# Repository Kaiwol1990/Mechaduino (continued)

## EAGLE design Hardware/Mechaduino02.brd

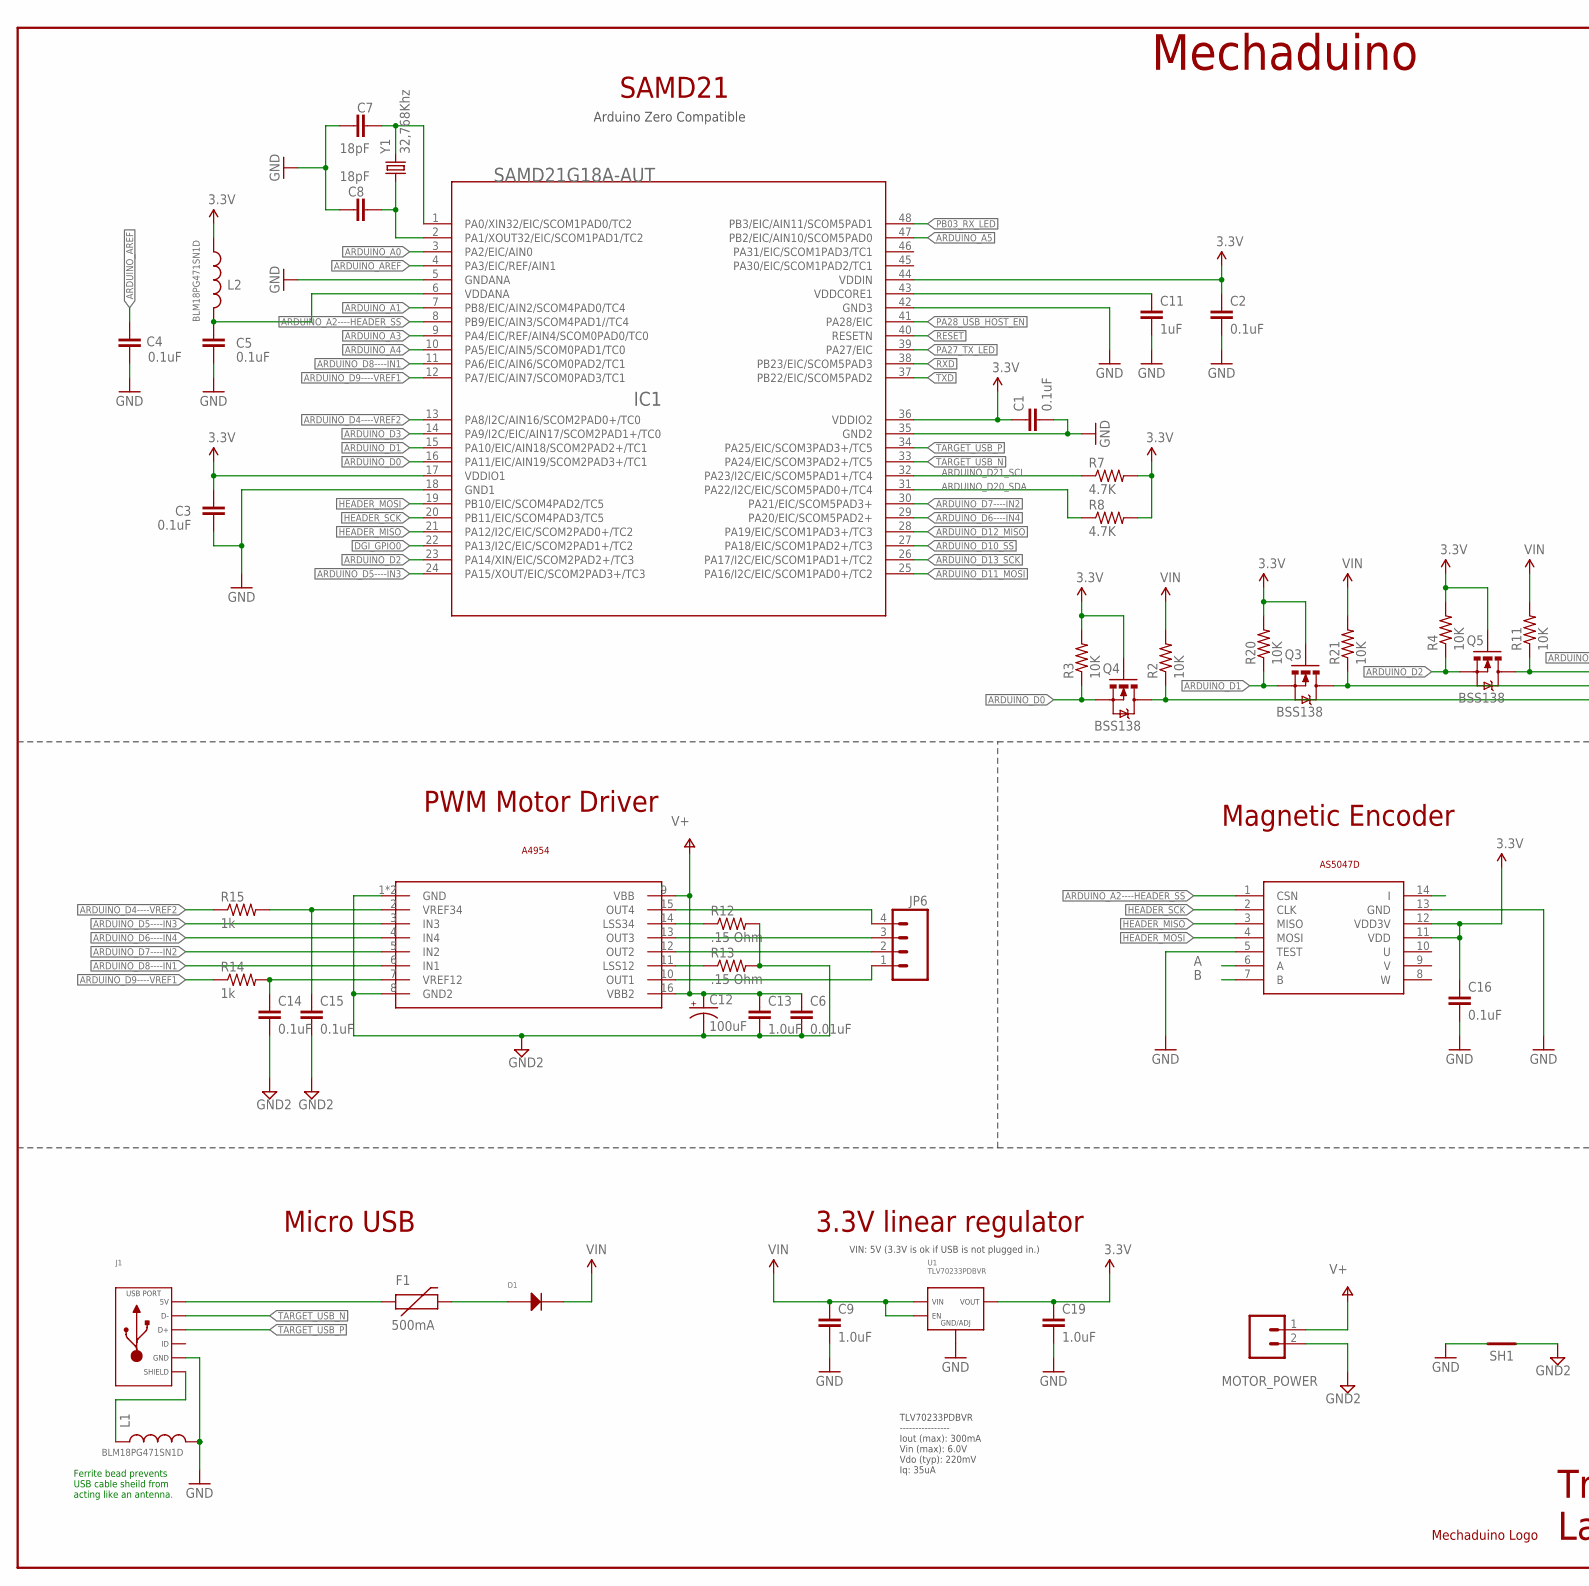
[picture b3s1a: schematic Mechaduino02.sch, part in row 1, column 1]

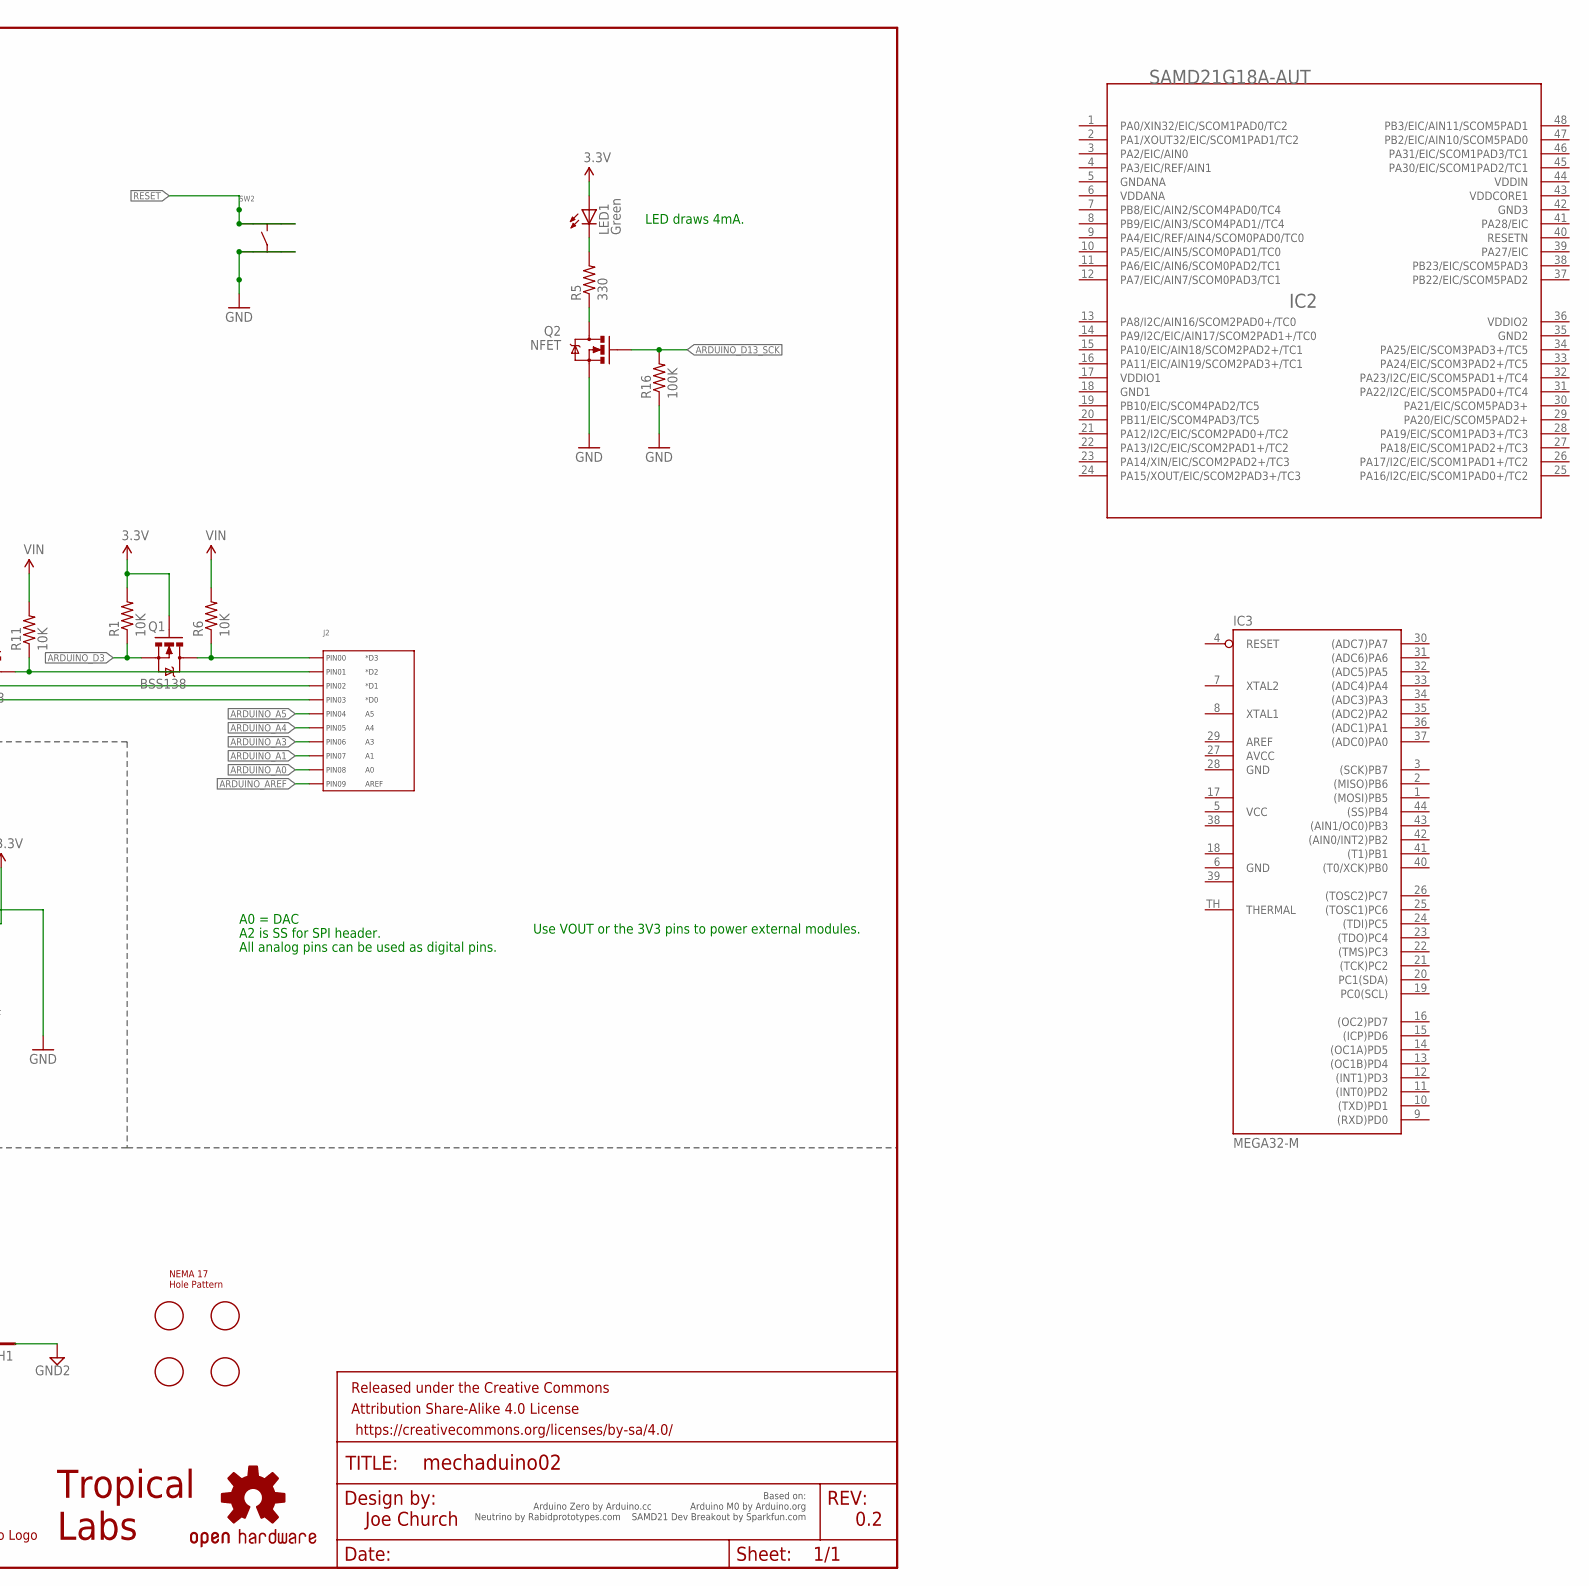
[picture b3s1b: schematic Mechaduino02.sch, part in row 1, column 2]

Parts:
C1, C2, C3, C4, C5, C14, C15, C16: 0.1uF; 0402-CAP
C6: 0.01uF; 0603-CAP
C7, C8: 18pF; 0603-CAP
C9, C19: 1.0uF; 0402-CAP
C11: 1uF; 0402-CAP
C12: 100uF; PANASONIC_D
C13: 1.0uF; 0603-CAP
D1: DIODE_SOD-123; SOD-123
F1: 500mA; PTC-1206
FRAME1: FRAME-LEDGER; CREATIVE_COMMONS
IC1, IC2: SAMD21G18A-AUT; INTEGRATEDCIRCUITS_TQFP48-7X7
IC3: MEGA32-M; MLF44-TH
J1: USB_MICRO_RIGHT; MICROUSB-RIGHT
J2: HEADER_01X10_PTH_2.54MM; PTH_2.54MM_01X10
JP6: M04PTH; 1X04
L1, L2: BLM18PG471SN1D; 0603-TDK
LED1: Green; CHIPLED_0805
LOGO4: OSHW-LOGOMOD; OSHW_LOGO_COPPER_MOD
MOTOR_POWER: M025MM; SCREWTERMINAL-5MM-2
Q1, Q3, Q4, Q5: BSS138; SOT23-3
Q2: NFET; SOT323
R1, R2, R3, R4, R6, R11, R20, R21: 10K; R0402-VISHAY
R5: 330; R0402-VISHAY
R7, R8: 4.7K; R0402-VISHAY
R12, R13: .15 Ohm; R1206
R14, R15: 1k; R0402-VISHAY
R16: 100K; R0402-VISHAY
SH1: SHORT-HA5; SHORT_ALL-50
SW2: TACT_4.2MM; TACT4.2MM
U1: TLV70233PDBVR; SOT-23-5
U$1: AVAGO_DRIVERTHERM; TSSOP16_THERM
U$2: NEMA17_HOLE_PATTERNNEW; NEMA17_HOLE_PATTERN_2
U$3: TROPICAL_LABS_LOGO_1LOGO3; LOGO3
U$4: AS5047D; TSSOP14
U$5: MECHADUINO_LOGO
Y1: 32,768Khz; CRYSTAL-SMD-2.0X1.2

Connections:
3.3V: C1.1, C2.1, C3.2, C16.1, C19.1, IC1.17 (VDDIO1), IC1.36 (VDDIO2), IC1.44 (VDDIN), L2.1, LED1.A, Q1.1 (G), Q3.1 (G), Q4.1 (G), Q5.1 (G), R1.2, R3.2, R4.2, R7.2, R8.2, R20.2, U1.P$5 (VOUT), U$4.11 (VDD), U$4.12 (VDD3V)
A: U$4.6 (A)
ARDUINO_A0: IC1.3 (PA2/EIC/AIN0), J2.P$9 (PIN8)
ARDUINO_A1: IC1.7 (PB8/EIC/AIN2/SCOM4PAD0/TC4), J2.P$8 (PIN7)
ARDUINO_A2----HEADER_SS: IC1.8 (PB9/EIC/AIN3/SCOM4PAD1//TC4), U$4.1 (CSN)
ARDUINO_A3: IC1.9 (PA4/EIC/REF/AIN4/SCOM0PAD0/TC0), J2.P$7 (PIN6)
ARDUINO_A4: IC1.10 (PA5/EIC/AIN5/SCOM0PAD1/TC0), J2.P$6 (PIN5)
ARDUINO_A5: IC1.47 (PB2/EIC/AIN10/SCOM5PAD0), J2.P$5 (PIN4)
ARDUINO_AREF: C4.1, IC1.4 (PA3/EIC/REF/AIN1), J2.P$10 (PIN9)
ARDUINO_D0: IC1.16 (PA11/EIC/AIN19/SCOM2PAD3+/TC1), Q4.2 (S), R3.1
ARDUINO_D1: IC1.15 (PA10/EIC/AIN18/SCOM2PAD2+/TC1), Q3.2 (S), R20.1
ARDUINO_D2: IC1.23 (PA14/XIN/EIC/SCOM2PAD2+/TC3), Q5.2 (S), R4.1
ARDUINO_D3: IC1.14 (PA9/I2C/EIC/AIN17/SCOM2PAD1+/TC0), Q1.2 (S), R1.1
ARDUINO_D4----VREF2: IC1.13 (PA8/I2C/AIN16/SCOM2PAD0+/TC0), R15.1
ARDUINO_D5----IN3: IC1.24 (PA15/XOUT/EIC/SCOM2PAD3+/TC3), U$1.3 (IN3)
ARDUINO_D6----IN4: IC1.29 (PA20/EIC/SCOM5PAD2+), U$1.4 (IN4)
ARDUINO_D7----IN2: IC1.30 (PA21/EIC/SCOM5PAD3+), U$1.5 (IN2)
ARDUINO_D8----IN1: IC1.11 (PA6/EIC/AIN6/SCOM0PAD2/TC1), U$1.6 (IN1)
ARDUINO_D9----VREF1: IC1.12 (PA7/EIC/AIN7/SCOM0PAD3/TC1), R14.1
ARDUINO_D10_SS: IC1.27 (PA18/EIC/SCOM1PAD2+/TC3)
ARDUINO_D11_MOSI: IC1.25 (PA16/I2C/EIC/SCOM1PAD0+/TC2)
ARDUINO_D12_MISO: IC1.28 (PA19/EIC/SCOM1PAD3+/TC3)
ARDUINO_D13_SCK: IC1.26 (PA17/I2C/EIC/SCOM1PAD1+/TC2), Q2.1 (G), R16.2
ARDUINO_D20_SDA: IC1.31 (PA22/I2C/EIC/SCOM5PAD0+/TC4), R8.1
ARDUINO_D21_SCL: IC1.32 (PA23/I2C/EIC/SCOM5PAD1+/TC4), R7.1
AVCC: IC3.27 (AVCC)
B: U$4.7 (B)
DGI_GPIO0: IC1.22 (PA13/I2C/EIC/SCOM2PAD1+/TC2)
GND: C1.2, C2.2, C3.1, C4.2, C5.2, C7.1, C8.1, C9.2, C11.2, C16.2, C19.2, IC1.5 (GNDANA), IC1.18 (GND1), IC1.35 (GND2), IC1.42 (GND3), IC3.6 (GND), IC3.28 (GND), J1.5 (GND), L1.2, Q2.2 (S), R16.1, SH1.2, SW2.P$3, SW2.P$4, U1.P$2 (GND/ADJ), U$4.5 (TEST), U$4.13 (GND)
GND1: IC2.18 (GND1), IC3.18 (GND1)
GND2: C6.2, C12.-, C13.2, C14.2, C15.2, IC2.35 (GND2), IC3.39 (GND2), MOTOR_POWER.2, R12.2, R13.2, SH1.1, U$1.1 (GND), U$1.8 (GND2), U$1.P$1 (GND)
GND3: IC2.42 (GND3)
GNDANA: IC2.5 (GNDANA)
HEADER_MISO: IC1.21 (PA12/I2C/EIC/SCOM2PAD0+/TC2), U$4.3 (MISO)
HEADER_MOSI: IC1.19 (PB10/EIC/SCOM4PAD2/TC5), U$4.4 (MOSI)
HEADER_SCK: IC1.20 (PB11/EIC/SCOM4PAD3/TC5), U$4.2 (CLK)
HV1: J2.P$3 (PIN2), Q3.3 (D), R21.1
HV2: J2.P$4 (PIN3), Q4.3 (D), R2.1
HV3: J2.P$2 (PIN1), Q5.3 (D), R11.1
HV4: J2.P$1 (PIN0), Q1.3 (D), R6.1
I: U$4.14 (I)
unnamed: LED1.C, R5.2
unnamed: R12.1, U$1.14 (LSS34)
unnamed: Q2.3 (D), R5.1
unnamed: R13.1, U$1.11 (LSS12)
unnamed: C15.1, R15.2, U$1.2 (VREF34)
unnamed: JP6.4, U$1.15 (OUT4)
unnamed: JP6.1, U$1.10 (OUT1)
unnamed: JP6.2, U$1.12 (OUT2)
unnamed: JP6.3, U$1.13 (OUT3)
unnamed: C14.1, R14.2, U$1.7 (VREF12)
unnamed: D1.ANODE, F1.2
unnamed: F1.1, J1.1 (5V)
PA00_XIN32: C7.2, IC1.1 (PA0/XIN32/EIC/SCOM1PAD0/TC2), Y1.2
PA01_XOUT32: C8.2, IC1.2 (PA1/XOUT32/EIC/SCOM1PAD1/TC2), Y1.1
PA27_TX_LED: IC1.39 (PA27/EIC)
PA28_USB_HOST_EN: IC1.41 (PA28/EIC)
PB03_RX_LED: IC1.48 (PB3/EIC/AIN11/SCOM5PAD1)
RESET: IC1.40 (RESETN), SW2.P$1, SW2.P$2
RXD: IC1.38 (PB23/EIC/SCOM5PAD3)
SHIELD: J1.S1 (SLD), J1.S2 (SLD), J1.S3 (SLD), J1.S4 (SLD), J1.S5 (SLD), J1.S6 (SLD), J1.S7 (SLD), J1.S8 (SLD), L1.1
TARGET_USB_N: IC1.33 (PA24/EIC/SCOM3PAD2+/TC5), J1.2 (D-)
TARGET_USB_P: IC1.34 (PA25/EIC/SCOM3PAD3+/TC5), J1.3 (D+)
TXD: IC1.37 (PB22/EIC/SCOM5PAD2)
V+: C6.1, C12.+, C13.1, MOTOR_POWER.1, U$1.9 (VBB), U$1.16 (VBB2)
VCC: IC3.5 (VCC)
VCC1: IC3.17 (VCC1)
VCC2: IC3.38 (VCC2)
VDDANA: C5.1, IC1.6 (VDDANA), IC2.6 (VDDANA), L2.2
VDDCORE: C11.1, IC1.43 (VDDCORE1)
VDDIN: IC2.44 (VDDIN)
VDDIO1: IC2.17 (VDDIO1)
VDDIO2: IC2.36 (VDDIO2)
VIN: C9.1, D1.CATHODE, R2.2, R6.2, R11.2, R21.2, U1.P$1 (VIN), U1.P$3 (EN)

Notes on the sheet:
A0 = DAC
All analog pins can be used as digital pins.
LED draws 4mA.
A2 is SS for SPI header.
Use VOUT or the 3V3 pins to power external modules.
Ferrite bead prevents USB cable sheild from acting like an antenna.
3.3V linear regulator
Magnetic Encoder
SAMD21
PWM Motor Driver
VIN: 5V (3.3V is ok if USB is not plugged in.)
TLV70233PDBVR ---------------- Iout (max): 300mA Vin (max): 6.0V Vdo (typ): 220mV Iq: 35uA
A4954
Micro USB
Joe Church
Based on: Arduino Zero by Arduino.cc Arduino M0 by Arduino.org Neutrino by Rabidprototypes.com SAMD21 Dev Breakout by Sparkfun.com
0.2
Arduino Zero Compatible
Mechaduino

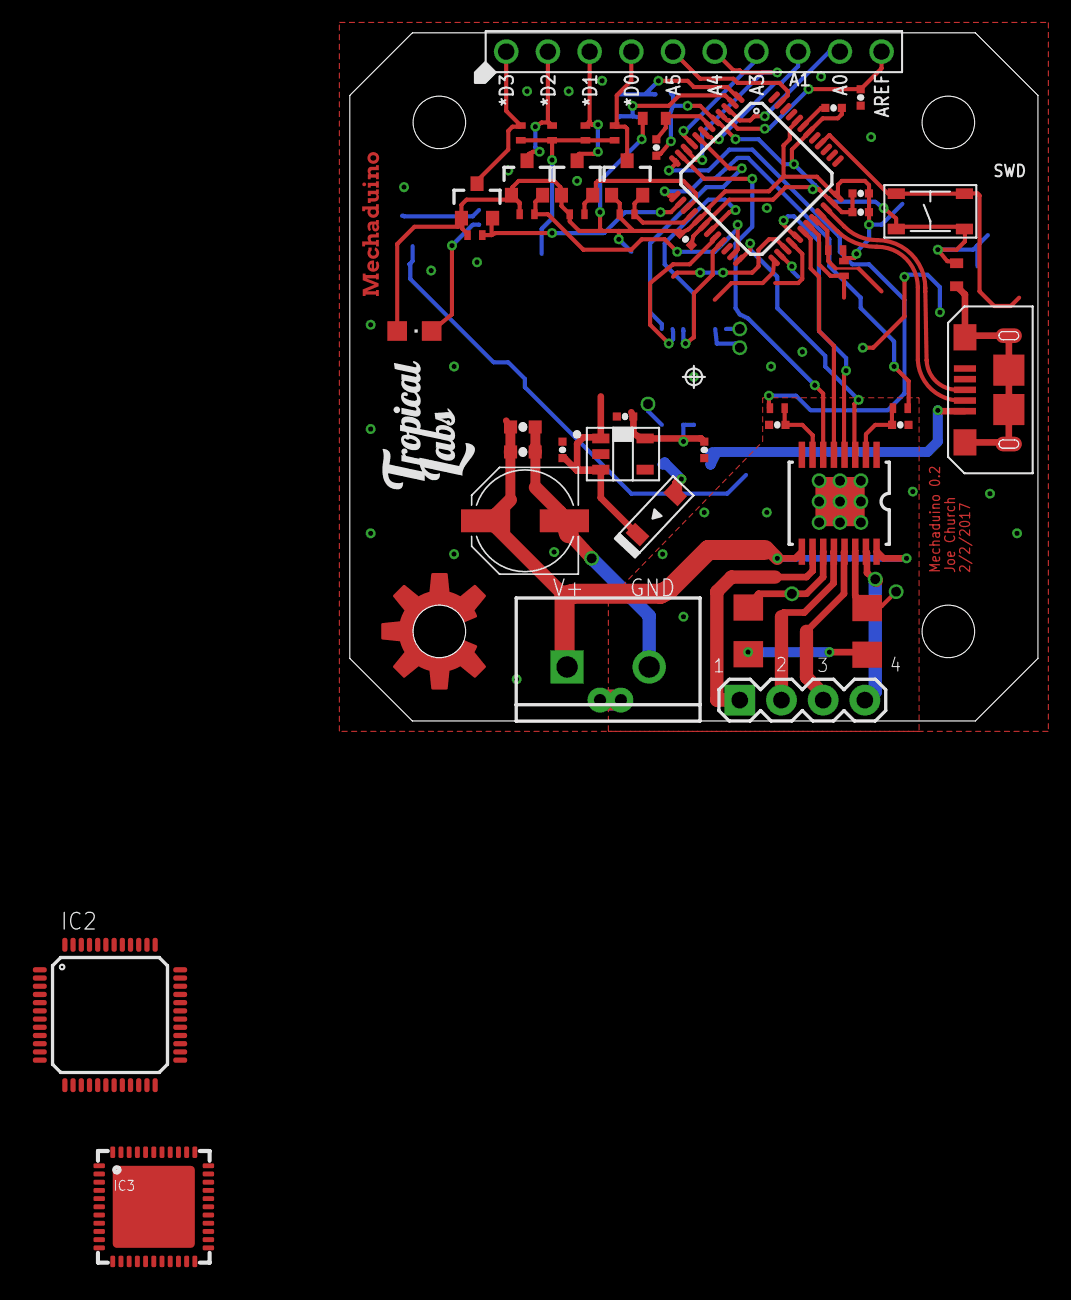
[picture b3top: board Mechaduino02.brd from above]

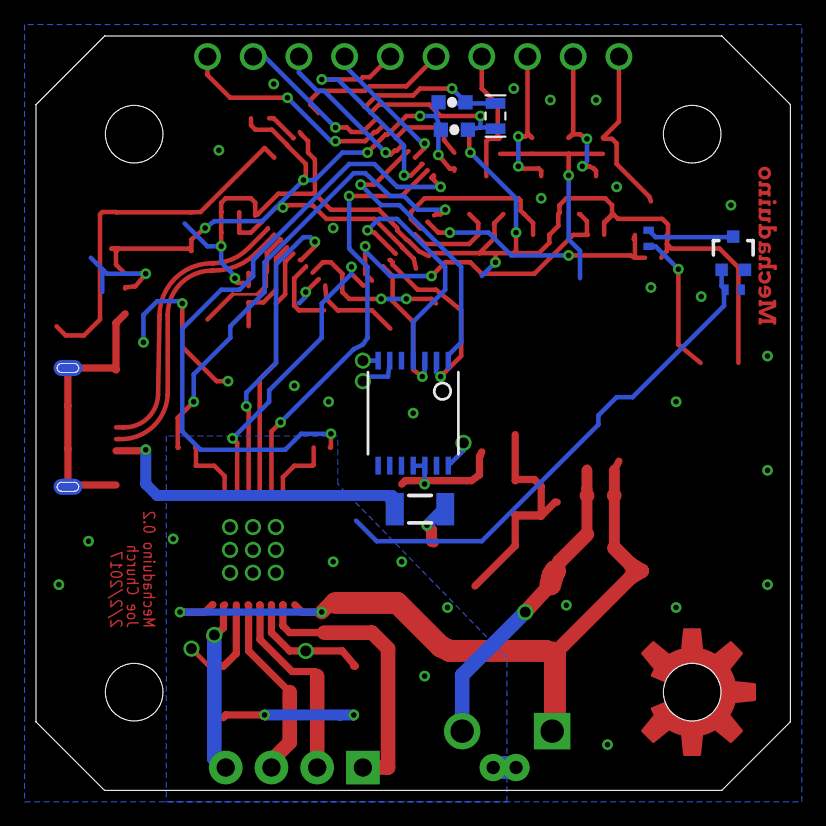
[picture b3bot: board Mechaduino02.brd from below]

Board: 2 copper layers, 41.9 x 41.9 mm, 60 parts (8 on the bottom side), 53 nets.

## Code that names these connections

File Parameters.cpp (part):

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//////////////////PINS////////////////
//////////////////////////////////////

const int IN_4 = 6; //PA20
const int IN_3 = 5; //PA15
const int VREF_2 = 4; //PA08
const int VREF_1 = 9; //PA07
const int IN_2 = 7; //PA21
const int IN_1 = 8; //PA06
const int ledPin = 13; //PA17
const int chipSelectPin = A2; //PB08

const int dir_pin = 0;
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
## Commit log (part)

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2016-10-22 Add files via upload
    - Added an digital filter for the error.
    - deletet all loops other then position
    - fixed some menu issues
    - added menu for an step response
2016-10-23 Add files via upload
    - deleted digital filter
    - changed digitalWrite commands to direct register manipulation (much faster)
    - changed frequenz from 3000 Hz to about 4500 Hz (no need for filtering anymore)
2016-10-23 Add files via upload
    Processing file to visualise the step responce of the system
2016-10-23 Rename Controller.cpp to Mechaduino_01/Controller.cpp
2016-10-23 Rename step_response.pde to step_response/step_response.pde
2016-10-23 Rename README_1.md to step_response/README.md
2016-10-24 fixed calibration routine
2016-10-24 some changes in parameter.cpp
2016-10-24 changed some menus and made it easier to disable the enable pin
    - calibration routine now prints percent instead of encoder reading
    - enable pin can be disabled by simply setting it to -1
2016-10-24 minor changes
2016-10-24 no need to set the tep value it will be send from the mechaduino
2016-10-25 changed the ability to let the porcessing script send the step size, theres no need for reuploading the firmware anymore
2016-10-26 changed calibration routine to find zero point faster, added some time outs for the serial communication
2016-10-26 Stl to get the magnet closer to the motor shaft and to seperate it from the shaft
2016-10-28 Fixed some filtering errors that occured
2016-10-29 Changed filterfrom butterworth to biquad
    The biquad filter shows no overshoot, so theres les overshoot in the PID
    loop aswell.
    Also made it possible to change the filter frequence on the fly
2016-10-29 changed the frequency to allow more step inputs
2016-10-30 PID tuned
2016-10-31 implemented an IIR Filter instead of an biquad for faster performance, cleanup
2016-10-31 some changes
2016-10-31 version with moving average added
2016-11-01 changed all variables to integer instead of float to get much higher performance
2016-11-01 fixed the setpoint function
2016-11-01 fixed overflow error for controller effor
2016-11-01 Merged Development in master
2016-11-01 Renamed some variables
2016-11-03 Changed more floats to int and multiplications to bitshifts
2016-11-03 Fixed an bitshift error
2016-11-18 added donation button
2016-11-18 fixed some plot bugs
2016-11-18 Clean up
    - added some comments
    - cleaned variables
    - cleaned #includes
    - cleaned utils.cpp
2016-11-18 Changed the PWM resolution to 12 bit
    The SAM21 can write PWM values with 12 bit instead of 8 bit, so we get much better resolutions for the coil currents with 12 bit and also much better control over the max current.
    example:
    i_max = 0.6 Amps
    with 8 bit pwm settings from 0 to max 69
    with 12 bit pwm settings from 0 to 1117
2016-11-18 Merged Dev in Master
2016-11-19 Added an Autotune function
    It's not workin perfectly but it gives some number so work with.
2016-11-19 changed some menu entrys
2016-11-19 calculationg the classic pid values to one with less overshoot
2016-11-19 reading the angle without DAEC to get less noise
2016-11-19 changed DAEC back got some strange bugs
2016-11-19 added an minimal cutoff current
    changed some parameters and added an minimal cutoff current
2016-11-19 changed all unnecessary floats to integer runs much faster now
2016-11-20 Fixed some major problems with the autotune function
2016-11-20 adapted for new firmware
2016-11-20 upload
2016-11-20 small changes for better performance
2016-11-21 Added support for the NZS misfittech.net
2016-11-21 added folder for NZS support
2016-11-21 relocation
2016-11-21 reupload of normal version
2016-11-21 renamed the analogfastwrite
2016-11-22 Some code cleanup
2016-11-23 rewritten the whole autotune function to use another (more stable) method
    changed the autotune method from an interactive type to a passive.
    At first the system will be oscillated and then this oscillation will be
    analyzed and based on that calculation the PID settings will be
    calculated.
2016-11-23 bugfix for 400 step motors
2016-11-23 potential bugfix for 400 steps motors
2016-11-24 bugfix for 400 step/rev motor
2016-11-25 changed the frequency detection to a better way
2016-11-25 Merge
2016-11-25 Changed PID frequency and made it easyer to change o 400 steps/rev motors
2016-11-25 deleted some delay and changed some variables to int for faster performance
2016-11-25 small bugfix
2016-11-26 added cos_lookup for coil current and made the pid autotune faster
2016-11-26 some code cleanup and variable cleaning
2016-11-26 Chaged back to one pid loop
2016-11-26 calculating maximal ITerm based on PID settings
2016-11-27 changed stepangle from int to float to get more accurate target calculation
    if using high microstepping the stepangel gets too small to perform
    integer calculations, so i changed it to float. makes everything a
    little slower (can get up to 18 kHz with 200 steps/mm an 200 mm/s) but
    gives more precision.
2016-11-27 typo
2016-12-01 small changes to the pid autotune
2016-12-06 Some code cleanup and a second pid loop for small errors integrated
    Big cleanup of the Serial interface
2016-12-06 change for newer firmware version
2016-12-10 Big Update!
2016-12-10 Big Update
    Added language support (only english and german for now)
    Added an invert direction setting
    Added support for NZS (not testet jet)
    Big cleanup and improvment for the Serialinterface
2016-12-10 Rename README.me to README.md
2016-12-10 bug fixes after update
2016-12-13 further improvment of the Serial communication
2016-12-13 bug fix to accept negative values in the serial set function
2016-12-14 improvment of the serial communication
2016-12-26 Changed the serial communication
    still working on the pid autotune to improve the stability
2017-01-06 Filters and RAS added
    - Added some Filters to the PID loop
    - implemented an RAS.
    - feedforward loop integrated, since the RAS bufferst the target it's
    possible to calculate the target speed
2017-01-08 Added simple inertia term
2017-01-15 improved autotune and inertia compensation
    - now tunes friction aswell
    - inertia terms for rotor inertia and inertia of the load
    - better configuration file layout
2017-01-15 small bug fix
2017-01-19 Updated the calibration to run 3 loops and avarage the readings, gives better results
2017-01-20 further improvment for the calibration
2017-01-21 fixed editparam menu and further improvment of the calibration
2017-01-23 small Bug fixes
2017-01-24 added dynamic phase advance term (early state)
2017-01-27 fix for overflow at high angles and dynamic phase advance
2017-01-27 bug fix for high angles
2017-01-29 deleted PIV setting
    deleted PIV setting since the controller works all the time with the velocity
2017-01-29 small changes
    the calibration routine prints the original mesaured values for the
    fullstep positons
2017-02-03 bootscreen fix
2017-02-03 bug fix in the inertia compensation terms
2017-02-04 small cleanup
2017-02-04 added check routine for the lookup table
2017-02-22 edit of the boot to start the motor without jerking at boot
2017-03-09 some small changes
    - the step response now also plots the target angle
    - there is a streaming option that outputs some parameters all the time while it's active
    - some changes to the pid loop speed
2017-03-24 Early Version of a new GUI
2017-03-24 Early Version of a new simple GUI
2017-04-01 updated GUI verison
    included Parameter edit tab
2017-04-01 added support for dynamic changing of settings
2017-04-04 added stepresponse to GUI
2017-04-10 implemented a simple state controller
2017-04-12 small changes to improve the state controller
2017-04-13 Update of the Readme
2017-04-13 Update of the GUI
    - Better autozoom for the live plots
    - ramp function to set the target with a ramp up instead of a jump
    - step response will be shown from zero to stepsize
2017-04-13 deleted the state controller since it was buggy
2017-05-01 bug fix for serial menus
    The serial menu allows now to change all low pass filter frequencies
2017-05-02 fixed error if no serial port is available
2017-05-02 fixed error in the datalogging function
2017-05-02 Streaming now works with about 250 Hz instead of 100 Hz
2017-05-02 Serial was streaming with 200 Hz instead of 250 Hz -> now fixed
2017-05-05 GUI and firmware update
    The GUI and new firmware now support to change the sample rate while
    performing a step response.
    The GUI now supports to export the collected data from a step respnse as
    csv or txt file.
    Note:
    The firmware need to be updated aswell.
2017-06-16 license file added
2017-06-22 Deleted some filters
2017-06-22 Deleted some filters and implemented an simple error register
2017-06-22 Error register and no more PROGMEM variables
    added an error "register" (bitwise errorflags in one integer)
    deleted all PROGMEM variables
2017-06-22 README upload
2017-06-22 readme update
2017-06-23 Folder renamed
2017-06-23 renamed folder
2017-06-23 moved file
2017-06-23 test
2017-06-23 change in LED pattern
2017-06-23 clean up
    - Deleted some unnecessary #include
    - Deleted some unnecessary variables
2017-06-23 deleted unused variables and clean up
2017-06-26 bugfix in auotune function
    deleted a line where the autotune function was called with the PID frequency -> restored that line should work again
2017-06-26 small typo
2017-06-26 added second pid controller for small errors and low velocity
    second pid loop pased on pessen variables
2017-07-22 gui update
    The gui can now plot more variables for tuning
    - velocity
    - velocity error
    - position and position error
    There is also a new test move pattern for motor tuning
2017-07-22 bug fix in the calibration routine
2017-07-24 GUI Update
    - It's now able to select the streamed variables. Also, there is the
    possibility to stream 2 variables in each plot.
    - Added an argument to the calibration routine to start it without a
    check of the direction
2017-07-30 Big Gui Update
    - The Gui supports now more features, like:
    - custom color for streaming
    - custom streaming selection
    - buffer for streamed variables, with overflow visualization
2017-08-10 GUI and Communication Update
    -new tab in the gui to run the downhill simplex algorithm, that tunes
    the pid settings
    - communication update. identifiert at the begining of streamed
    parameters for easier identification with the gui
2017-08-13 Complete rewritten Serial communication and GUI Update
    - The Serial accepts now arguments for the single commands -> see readme
    - The GUI has a new tab to control the autotune functions
2017-08-26 update of the Low pass filters involved in the A4954 code
2017-08-26 update of the low pass fitleres involved in the A4954 Driver code
2017-08-27 calibration update
    Added:
    - check argument to check the full step readings while calibrating
    - smooth argument to smooth the full step readings while calibrating
2017-08-28 bugfix in calibration
2017-08-31 Calibration moved to won cpp file
2018-04-26 changed microcontroller to ATSAMD51J19
2018-04-27 implemted voltage sense pin and some leds
2018-04-30 Rearange to fit old pin positions
2018-05-04 finished design
2018-05-07 Finalized version of PCB for manufacturing
